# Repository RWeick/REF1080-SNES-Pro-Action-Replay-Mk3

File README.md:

# REF1080-SNES-Pro-Action-Replay-Mk3
Everything necessary to produce the Datel Pro Action Replay Mk 3 for the SNES

PCB Thickness: 1.2 mm

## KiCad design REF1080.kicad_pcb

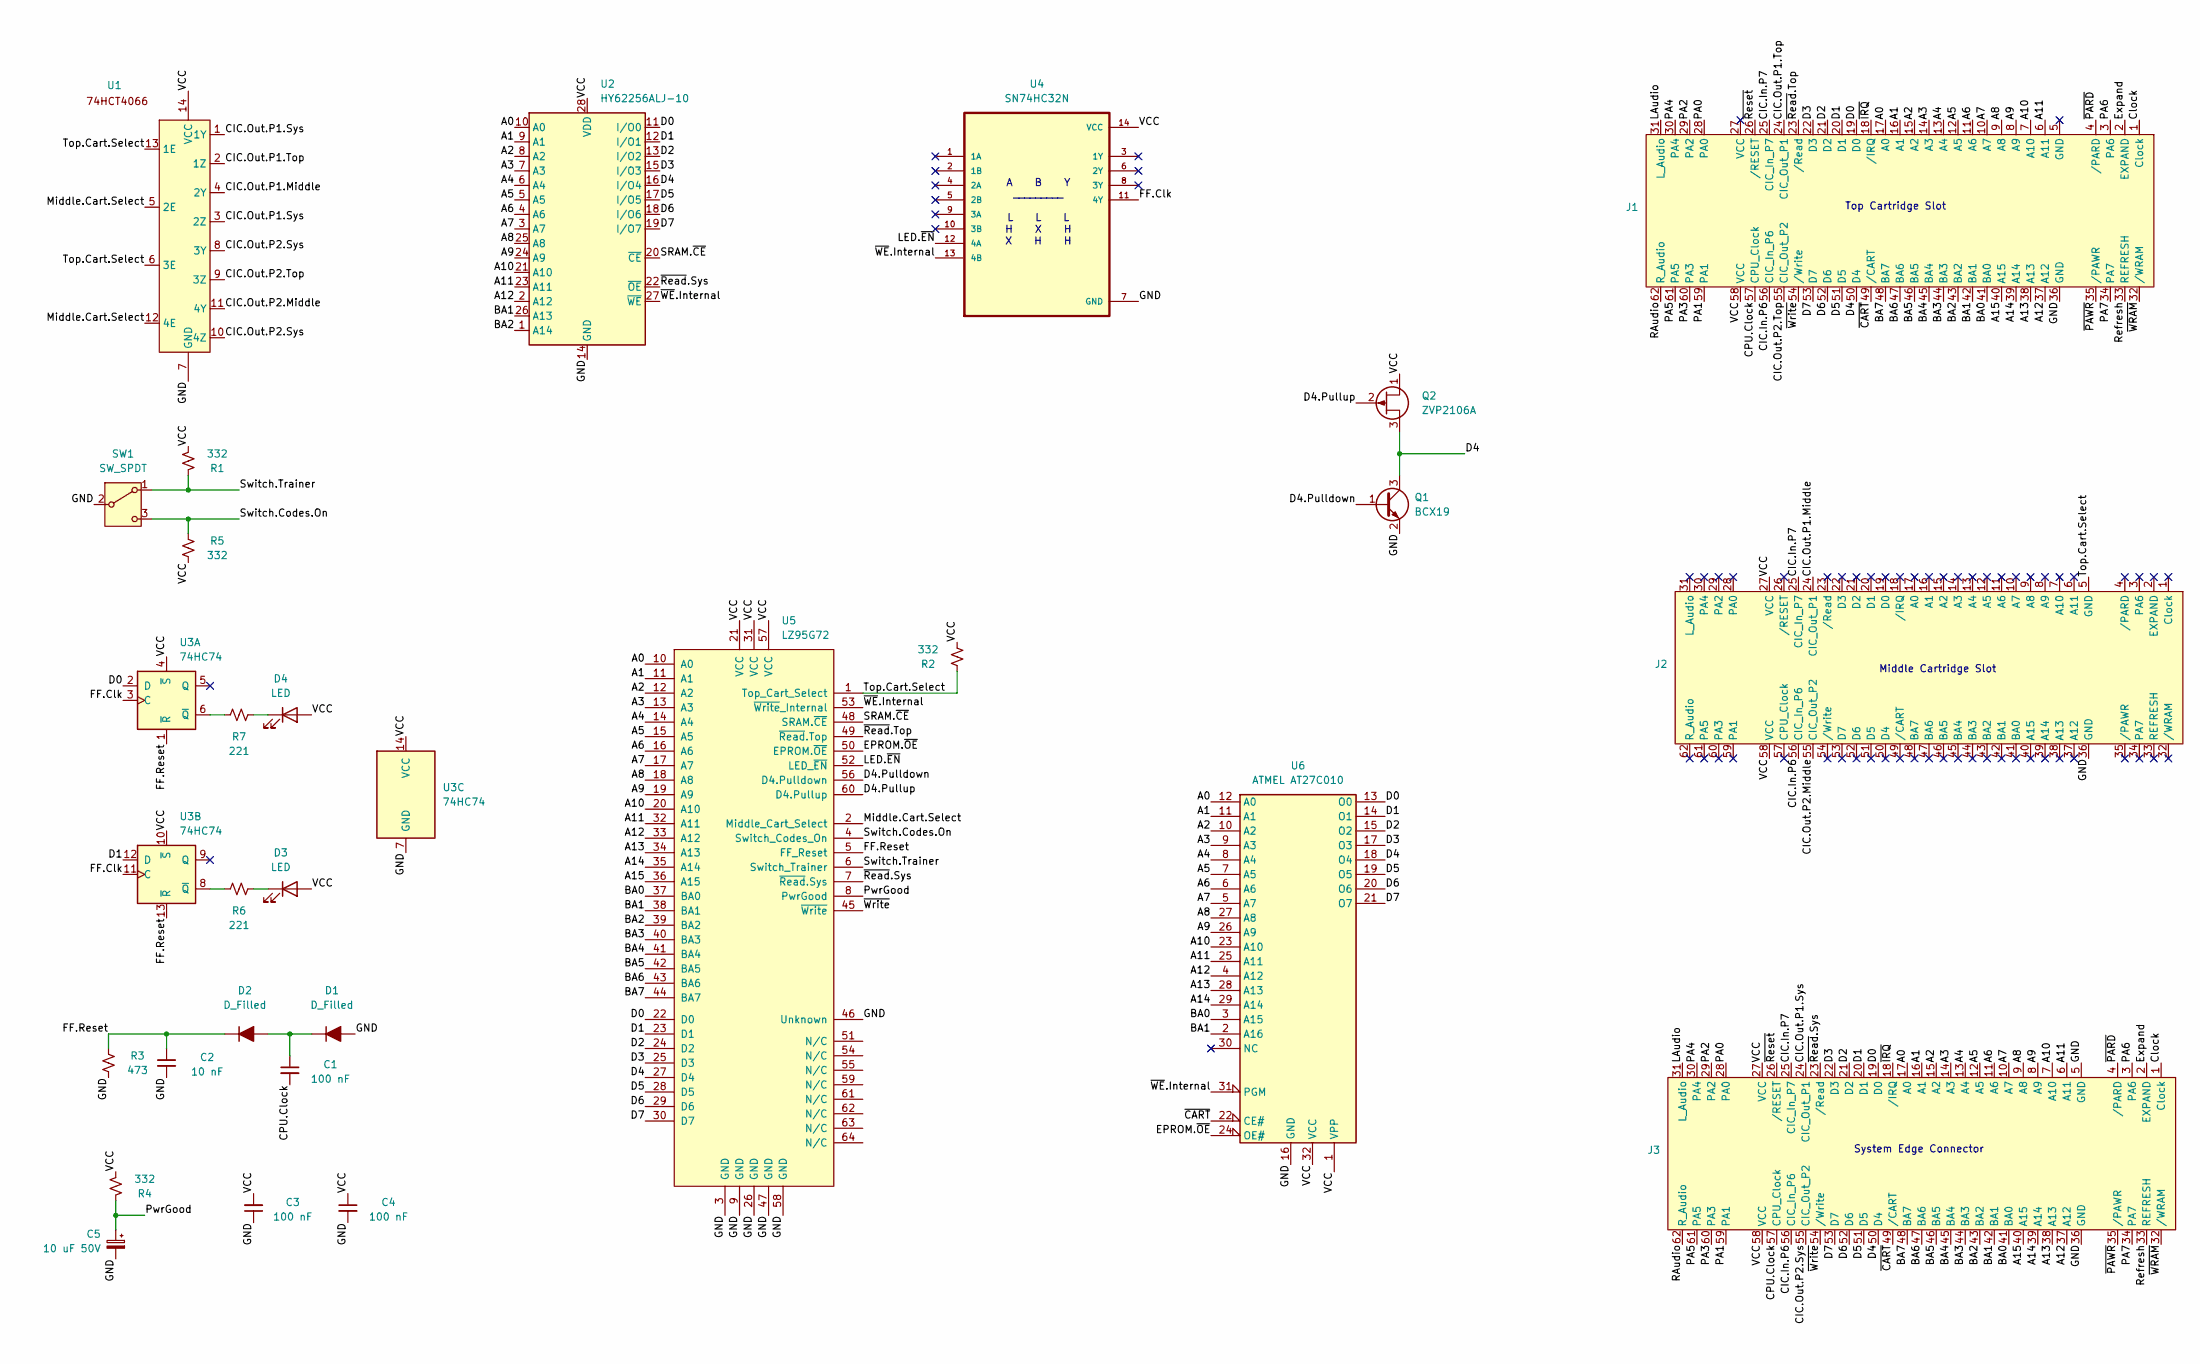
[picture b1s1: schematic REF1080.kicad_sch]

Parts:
C1, C3, C4: 100 nF; Capacitor
C2: 10 nF; Capacitor
C5: 10 uF 50V; CP_Radial_D5.0mm_P2.50mm
D1, D2: D_Filled; Diode
D3, D4: LED; LED_D1.8mm_W3.3mm_H2.4mm
J1: Top Edge Connector
J2: Middle Cartridge Slot
J3: Bottom Edge Connector
Q1: BCX19; SOT-23
Q2: ZVP2106A; TO-92Flat
R1, R2, R4, R5: 332; Resistor
R3: 473; Resistor
R6, R7: 221; Resistor
SW1: SW_SPDT; Switch
U1: SOIC-14
U2: HY62256ALJ-10; HY62256ALJ
U3: 74HC74; SOIC-14
U4: SN74HC32N; SOIC-14
U5: LZ95G72
U6: ATMEL AT27C010; AT27C010

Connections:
/A0: J1.17 (A0), J3.17 (A0), U2.10 (A0), U5.10 (A0), U6.12 (A0)
/A1: J1.16 (A1), J3.16 (A1), U2.9 (A1), U5.11 (A1), U6.11 (A1)
/A2: J1.15 (A2), J3.15 (A2), U2.8 (A2), U5.12 (A2), U6.10 (A2)
/A3: J1.14 (A3), J3.14 (A3), U2.7 (A3), U5.13 (A3), U6.9 (A3)
/A4: J1.13 (A4), J3.13 (A4), U2.6 (A4), U5.14 (A4), U6.8 (A4)
/A5: J1.12 (A5), J3.12 (A5), U2.5 (A5), U5.15 (A5), U6.7 (A5)
/A6: J1.11 (A6), J3.11 (A6), U2.4 (A6), U5.16 (A6), U6.6 (A6)
/A7: J1.10 (A7), J3.10 (A7), U2.3 (A7), U5.17 (A7), U6.5 (A7)
/A8: J1.9 (A8), J3.9 (A8), U2.25 (A8), U5.18 (A8), U6.27 (A8)
/A9: J1.8 (A9), J3.8 (A9), U2.24 (A9), U5.19 (A9), U6.26 (A9)
/A10: J1.7 (A10), J3.7 (A10), U2.21 (A10), U5.20 (A10), U6.23 (A10)
/A11: J1.6 (A11), J3.6 (A11), U2.23 (A11), U5.32 (A11), U6.25 (A11)
/A12: J1.37 (A12), J3.37 (A12), U2.2 (A12), U5.33 (A12), U6.4 (A12)
/A13: J1.38 (A13), J3.38 (A13), U5.34 (A13), U6.28 (A13)
/A14: J1.39 (A14), J3.39 (A14), U5.35 (A14), U6.29 (A14)
/A15: J1.40 (A15), J3.40 (A15), U5.36 (A15)
/BA0: J1.41 (BA0), J3.41 (BA0), U5.37 (BA0), U6.3 (A15)
/BA1: J1.42 (BA1), J3.42 (BA1), U2.26 (A13), U5.38 (BA1), U6.2 (A16)
/BA2: J1.43 (BA2), J3.43 (BA2), U2.1 (A14), U5.39 (BA2)
/BA3: J1.44 (BA3), J3.44 (BA3), U5.40 (BA3)
/BA4: J1.45 (BA4), J3.45 (BA4), U5.41 (BA4)
/BA5: J1.46 (BA5), J3.46 (BA5), U5.42 (BA5)
/BA6: J1.47 (BA6), J3.47 (BA6), U5.43 (BA6)
/BA7: J1.48 (BA7), J3.48 (BA7), U5.44 (BA7)
/CIC.In.P6: J1.56 (CIC_In_P6), J2.56 (CIC_In_P6), J3.56 (CIC_In_P6)
/CIC.In.P7: J1.25 (CIC_In_P7), J2.25 (CIC_In_P7), J3.25 (CIC_In_P7)
/CIC.Out.P1.Middle: J2.24 (CIC_Out_P1), U1.4 (2Y)
/CIC.Out.P1.Sys: J3.24 (CIC_Out_P1), U1.1 (1Y), U1.3 (2Z)
/CIC.Out.P1.Top: J1.24 (CIC_Out_P1), U1.2 (1Z)
/CIC.Out.P2.Middle: J2.55 (CIC_Out_P2), U1.11 (4Y)
/CIC.Out.P2.Sys: J3.55 (CIC_Out_P2), U1.8 (3Y), U1.10 (4Z)
/CIC.Out.P2.Top: J1.55 (CIC_Out_P2), U1.9 (3Z)
/CPU.Clock: C1.2, J1.57 (CPU_Clock), J3.57 (CPU_Clock)
/Clock: J1.1 (Clock), J3.1 (Clock)
/D0: J1.19 (D0), J3.19 (D0), U2.11 (I/O0), U3.2 (D), U5.22 (D0), U6.13 (O0)
/D1: J1.20 (D1), J3.20 (D1), U2.12 (I/O1), U3.12 (D), U5.23 (D1), U6.14 (O1)
/D2: J1.21 (D2), J3.21 (D2), U2.13 (I/O2), U5.24 (D2), U6.15 (O2)
/D3: J1.22 (D3), J3.22 (D3), U2.15 (I/O3), U5.25 (D3), U6.17 (O3)
/D4: J1.50 (D4), J3.50 (D4), Q1.3 (C), Q2.3 (S), U2.16 (I/O4), U5.27 (D4), U6.18 (O4)
/D4.Pulldown: Q1.1 (B), U5.56 (D4.Pulldown)
/D4.Pullup: Q2.2 (G), U5.60 (D4.Pullup)
/D5: J1.51 (D5), J3.51 (D5), U2.17 (I/O5), U5.28 (D5), U6.19 (O5)
/D6: J1.52 (D6), J3.52 (D6), U2.18 (I/O6), U5.29 (D6), U6.20 (O6)
/D7: J1.53 (D7), J3.53 (D7), U2.19 (I/O7), U5.30 (D7), U6.21 (O7)
/EPROM.~OE: U5.50 (EPROM.~OE), U6.24 (OE#)
/Expand: J1.2 (EXPAND), J3.2 (EXPAND)
/FF.Clk: U3.3 (C), U3.11 (C), U4.11 (4Y)
/FF.Reset: C2.1, D2.1 (K), R3.1, U3.1 (~R), U3.13 (~R), U5.5 (FF_Reset)
/GND: C2.2, C3.1, C4.2, C5.2, D1.2 (A), J1.36 (GND), J2.36 (GND), J3.5 (GND), J3.36 (GND), Q1.2 (E), R3.2, SW1.2 (B), U1.7 (GND), U2.14 (GND), U3.7 (GND), U4.7 (GND), U5.3 (GND), U5.9 (GND), U5.26 (GND), U5.46 (Unknown), U5.47 (GND), U5.58 (GND), U6.16 (GND)
/LAudio: J1.31 (L_Audio), J3.31 (L_Audio)
/LED.~EN: U4.12 (4A), U5.52 (LED_~EN)
/Middle.Cart.Select: U1.5 (2E), U1.12 (4E), U5.2 (Middle_Cart_Select)
/PA0: J1.28 (PA0), J3.28 (PA0)
/PA1: J1.59 (PA1), J3.59 (PA1)
/PA2: J1.29 (PA2), J3.29 (PA2)
/PA3: J1.60 (PA3), J3.60 (PA3)
/PA4: J1.30 (PA4), J3.30 (PA4)
/PA5: J1.61 (PA5), J3.61 (PA5)
/PA6: J1.3 (PA6), J3.3 (PA6)
/PA7: J1.34 (PA7), J3.34 (PA7)
/PwrGood: C5.1, R4.1, U5.8 (PwrGood)
/RAudio: J1.62 (R_Audio), J3.62 (R_Audio)
/Refresh: J1.33 (REFRESH), J3.33 (REFRESH)
/SRAM.~CE: U2.20 (~CE), U5.48 (SRAM.~CE)
/Switch.Codes.On: R5.1, SW1.3 (C), U5.4 (Switch_Codes_On)
/Switch.Trainer: R1.1, SW1.1 (A), U5.6 (Switch_Trainer)
/Top.Cart.Select: J2.5 (GND), R2.1, U1.6 (3E), U1.13 (1E), U5.1 (Top_Cart_Select)
/VCC: C3.2, C4.1, D3.2 (A), D4.2 (A), J1.58 (VCC), J2.27 (VCC), J2.58 (VCC), J3.27 (VCC), J3.58 (VCC), Q2.1 (D), R1.2, R2.2, R4.2, R5.2, U1.14 (VCC), U2.28 (VDD), U3.4 (~S), U3.10 (~S), U3.14 (VCC), U4.14 (VCC), U5.21 (VCC), U5.31 (VCC), U5.57 (VCC), U6.1 (VPP), U6.32 (VCC)
/~CART: J1.49 (/CART), J3.49 (/CART), U6.22 (CE#)
/~IRQ: J1.18 (/IRQ), J3.18 (/IRQ)
/~PARD: J1.4 (/PARD), J3.4 (/PARD)
/~PAWR: J1.35 (/PAWR), J3.35 (/PAWR)
/~Read.Sys: J3.23 (/Read), U2.22 (~OE), U5.7 (~Read.Sys)
/~Read.Top: J1.23 (/Read), U5.49 (~Read.Top)
/~Reset: J1.26 (/RESET), J3.26 (/RESET)
/~WE.Internal: U2.27 (~WE), U4.13 (4B), U5.53 (~Write_Internal), U6.31 (PGM)
/~WRAM: J1.32 (/WRAM), J3.32 (/WRAM)
/~Write: J1.54 (/Write), J3.54 (/Write), U5.45 (~Write)
unnamed: C1.1, D1.1 (K), D2.2 (A)
unnamed: D3.1 (K), R6.1
unnamed: D4.1 (K), R7.1
unnamed: R7.2, U3.6 (~Q)
unnamed: R6.2, U3.8 (~Q)

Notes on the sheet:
Top Cartridge Slot
System Edge Connector
Middle Cartridge Slot
A B Y _________ L L L H X H X H H

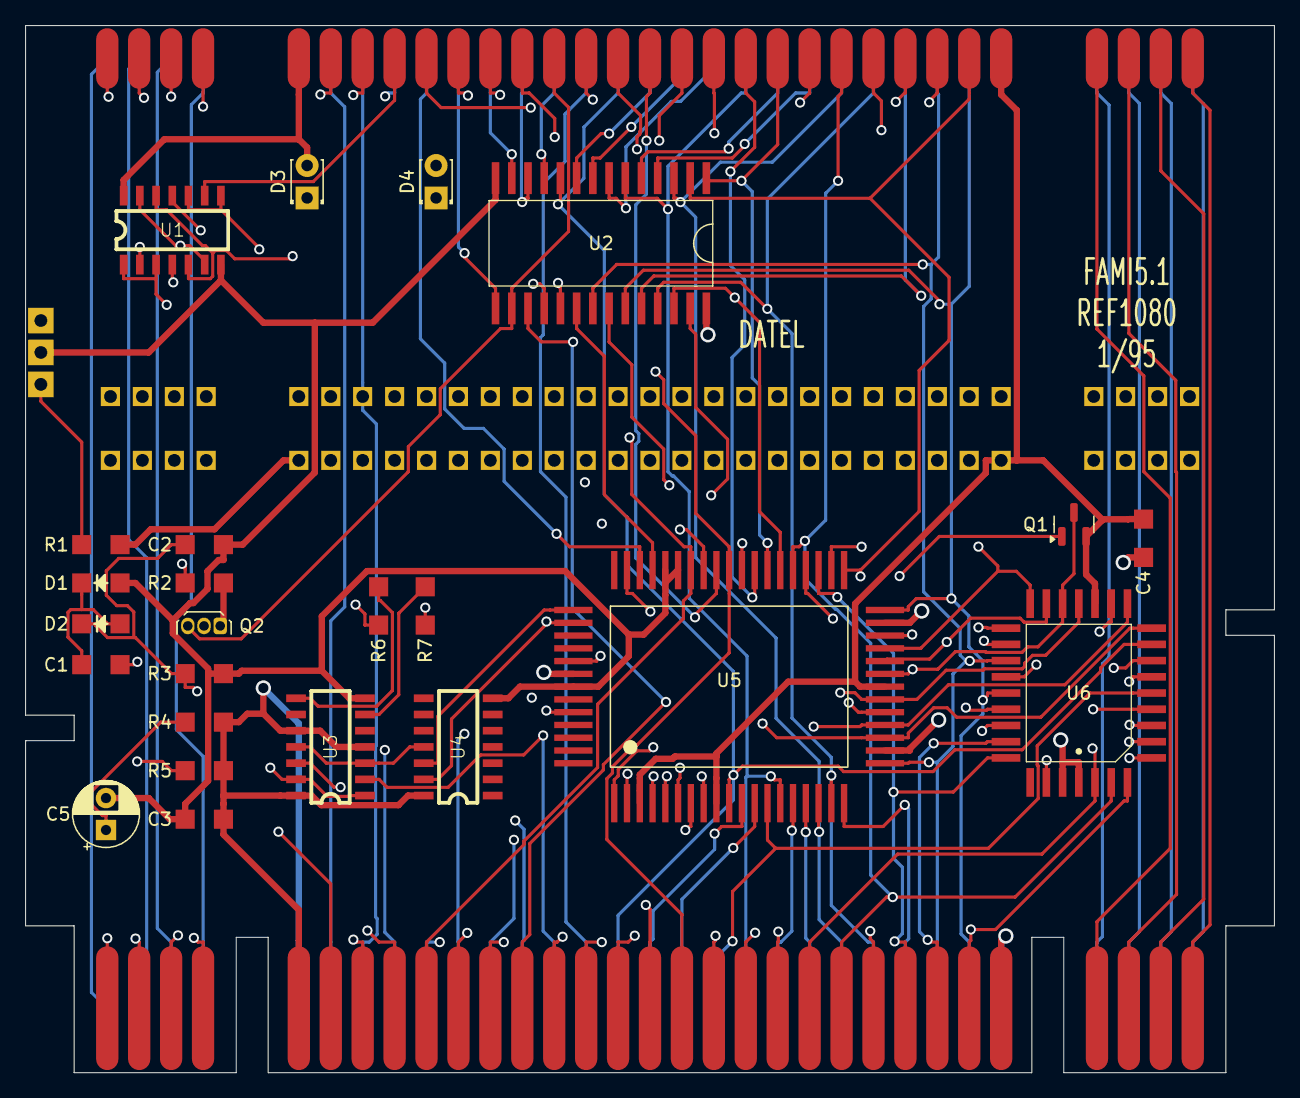
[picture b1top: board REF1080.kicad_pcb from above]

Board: 4 copper layers, 97.8 x 82.0 mm, 28 parts (0 on the bottom side), 83 nets.
